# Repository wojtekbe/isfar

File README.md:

isfar - H-ROV underwater robot
=====

Connectors
==========

I^2C (MICROMATCH-4):
--------
* 1 - SDA
* 2 - SCL
* 3 - GND
* 4 - +3V3

PWR (TBMP/C-GRID-03):
--------
* 1 - +5V
* 2 - GND
* 3 - +12V

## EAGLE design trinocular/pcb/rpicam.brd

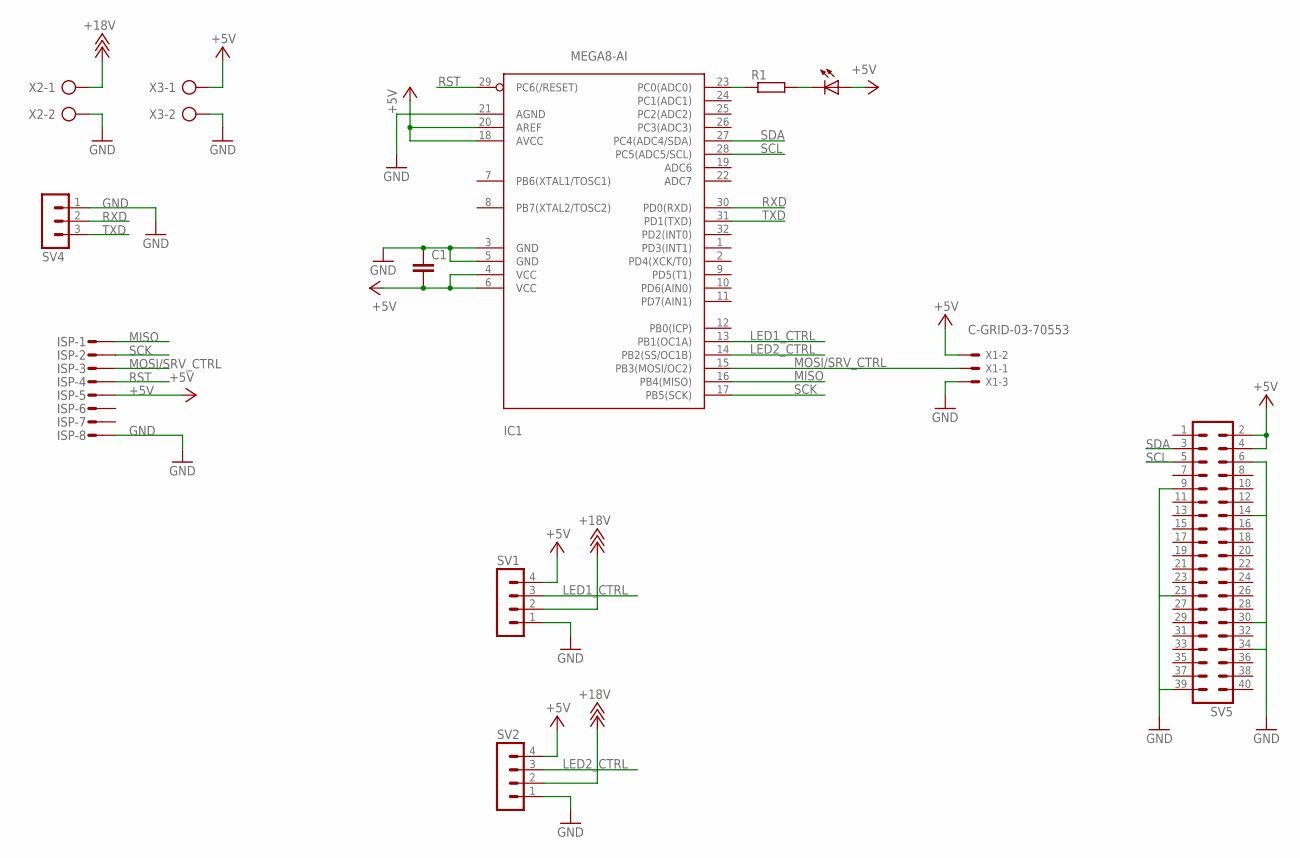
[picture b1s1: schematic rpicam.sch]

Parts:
C1: C-EUC0805; C0805
IC1: MEGA8-AI; TQFP32-08
ISP: MICROMATCH-8
LED1: LEDCHIP-LED0805; CHIP-LED0805
R1: R-EU_R0805; R0805
SV1, SV2: MA04-1
SV4: MA03-1
SV5: MA20-2
X1: C-GRID-03-70553; 70553-03
X2, X3: AK500/2

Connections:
+5V: C1.2, IC1.4 (VCC), IC1.6 (VCC), IC1.18 (AVCC), IC1.20 (AREF), ISP.5, LED1.A, SV1.4, SV2.4, SV5.2, SV5.4, X1.2, X3.1
+18V: SV1.2, SV2.2, X2.1
GND: C1.1, IC1.3 (GND), IC1.5 (GND), IC1.21 (AGND), ISP.8, SV1.1, SV2.1, SV4.1, SV5.6, SV5.9, SV5.14, SV5.25, SV5.30, SV5.34, SV5.39, X1.3, X2.2, X3.2
LED1_CTRL: IC1.13 (PB1(OC1A)), SV1.3
LED2_CTRL: IC1.14 (PB2(SS/OC1B)), SV2.3
MISO: IC1.16 (PB4(MISO)), ISP.1
MOSI/SRV_CTRL: IC1.15 (PB3(MOSI/OC2)), ISP.3, X1.1
unnamed: LED1.C, R1.2
unnamed: IC1.23 (PC0(ADC0)), R1.1
RST: IC1.29 (PC6(/RESET)), ISP.4
RXD: IC1.30 (PD0(RXD)), SV4.2
SCK: IC1.17 (PB5(SCK)), ISP.2
SCL: IC1.28 (PC5(ADC5/SCL)), SV5.5
SDA: IC1.27 (PC4(ADC4/SDA)), SV5.3
TXD: IC1.31 (PD1(TXD)), SV4.3

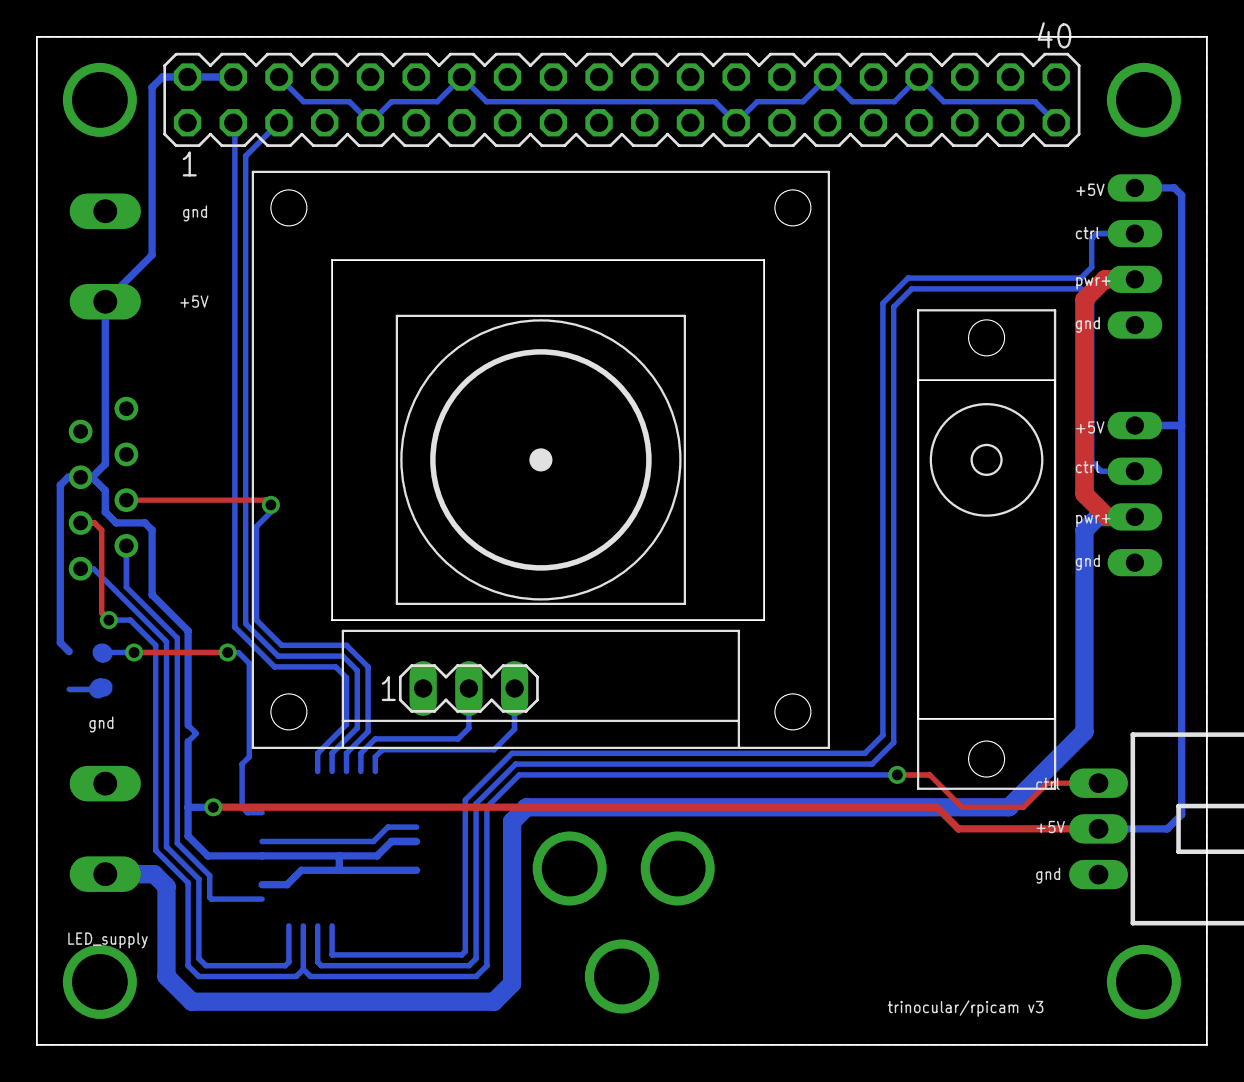
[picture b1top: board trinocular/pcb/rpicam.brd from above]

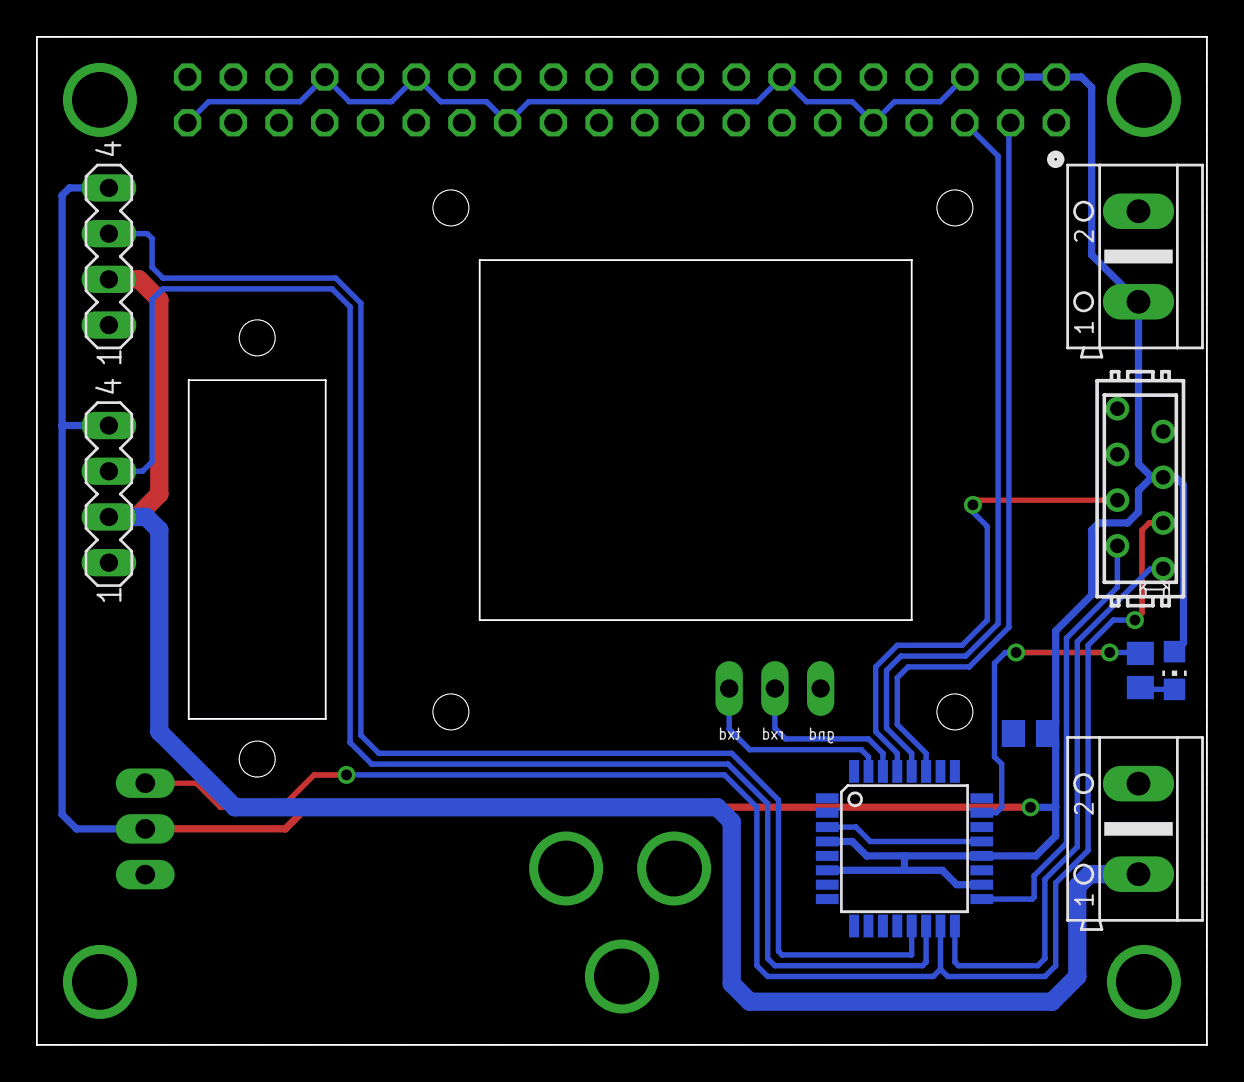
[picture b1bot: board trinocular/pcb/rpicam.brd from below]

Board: 2 copper layers, 65.0 x 56.0 mm, 14 parts (9 on the bottom side), 15 nets.

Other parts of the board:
U$3: HS-35HD
U$4: RPICAM_WAVESHARE

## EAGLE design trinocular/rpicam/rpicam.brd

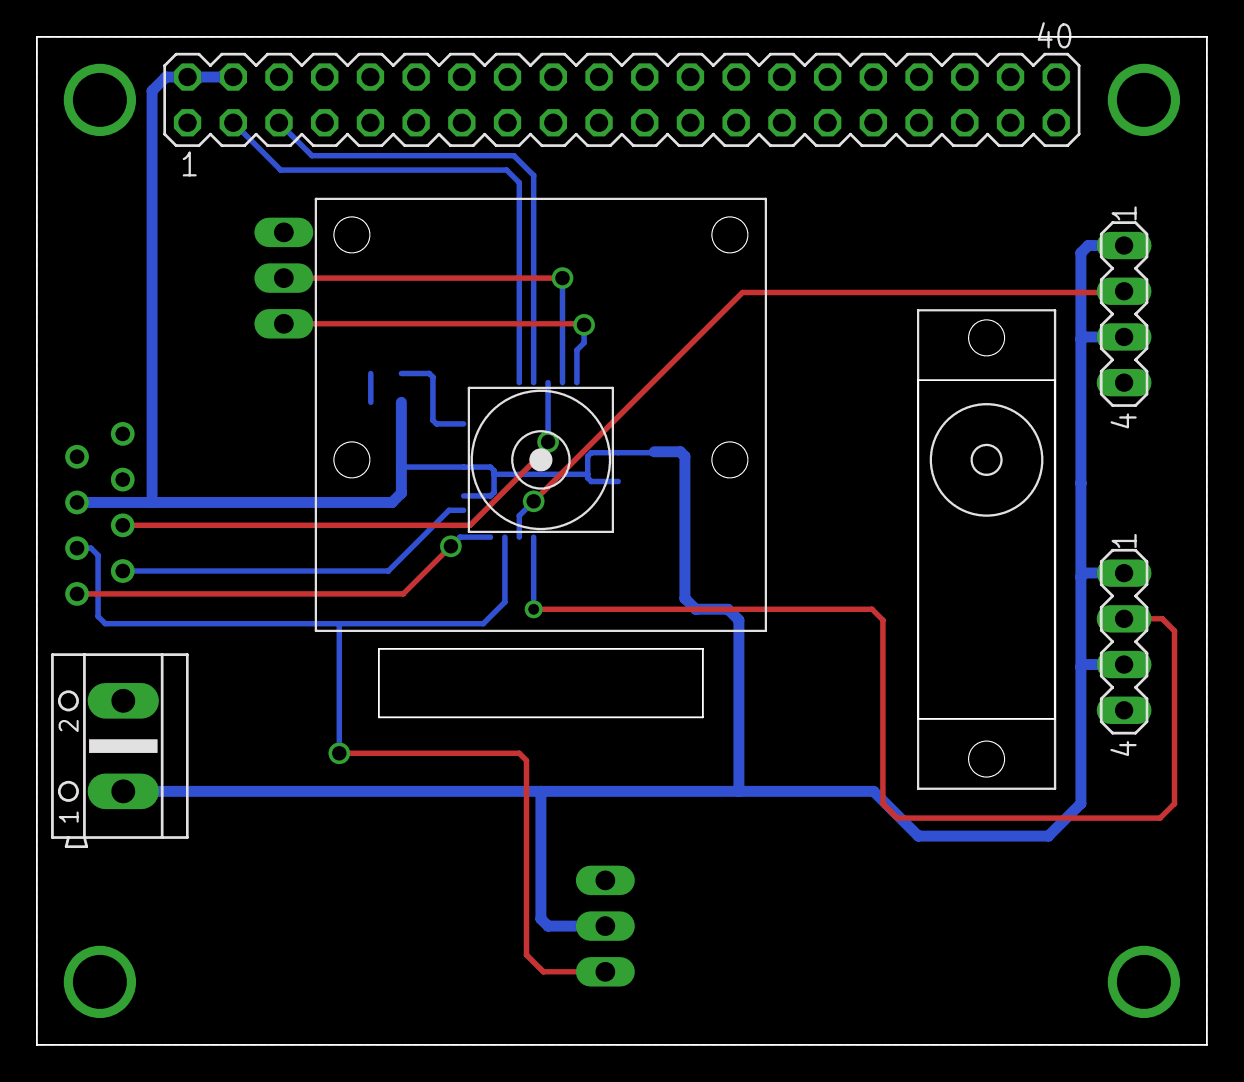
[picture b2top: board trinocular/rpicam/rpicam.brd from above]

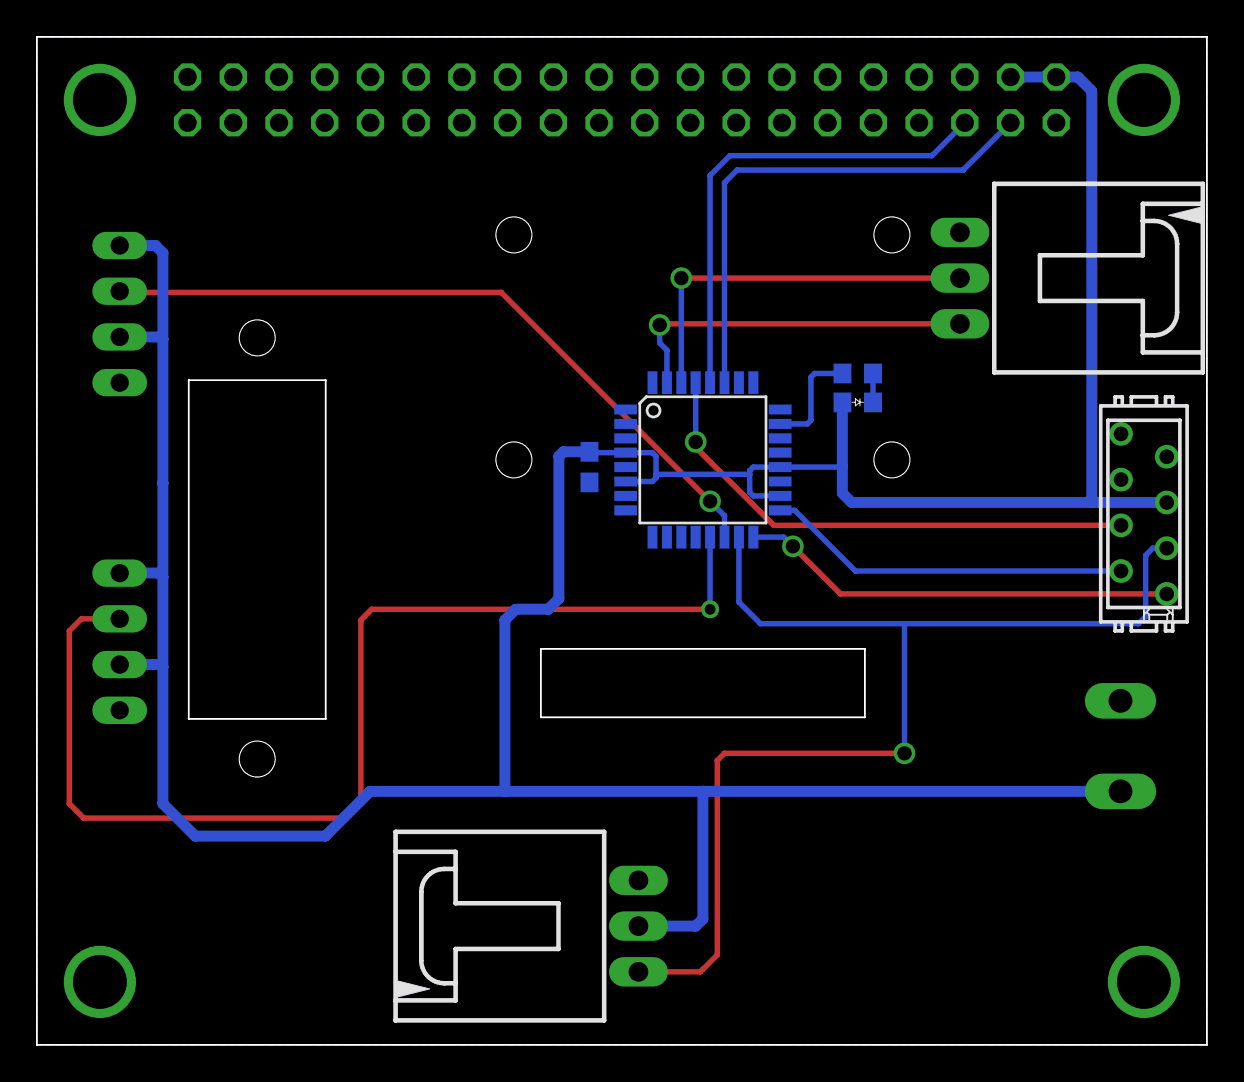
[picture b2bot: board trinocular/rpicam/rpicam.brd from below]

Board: 2 copper layers, 65.0 x 56.0 mm, 13 parts (7 on the bottom side), 14 nets.

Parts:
C1: C0603
IC1: MEGA8-AI; TQFP32-08
ISP: MICROMATCH-8
R1: R0603
SV1: MA20-2
SV2, SV3: MA04-1
U$1: LED0603; D0603
U$2: RPICAM
U$3: HS-35HD
UART: uart; 70553-03
X1: C-GRID-03-70553; 70553-03
X2: AK500/2

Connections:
+5V: C1.2, IC1.4, IC1.6, IC1.18, IC1.20, ISP.5, SV1.2, SV1.4, SV2.1, SV2.3, SV3.1, SV3.3, U$1.1, X1.2, X2.1
GND: C1.1, IC1.3, IC1.5, IC1.21, ISP.8, SV1.6, SV1.9, SV1.14, SV1.20, SV1.25, SV1.30, SV1.34, SV1.39, SV2.4, SV3.4, UART.1, X1.3, X2.2
LED1_CTRL: IC1.13, SV2.2
LED2_CTRL: IC1.14, SV3.2
MISO: IC1.16, ISP.1
MOSI/SRV_CTRL: IC1.15, ISP.3, X1.1
unnamed: R1.2, U$1.2
unnamed: IC1.23, R1.1
RST: IC1.29, ISP.4
RXD: IC1.30, UART.2
SCK: IC1.17, ISP.2
SCL: IC1.28, SV1.5
SDA: IC1.27, SV1.3
TXD: IC1.31, UART.3

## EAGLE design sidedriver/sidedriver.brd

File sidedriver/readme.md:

## GPIO Conf.

### M. Thruster

Name   | Pin | Func.
-------|-----|-----------
M1-PWM | PA1 | TIM2_CH2 
M1-CS  | PA2 | ADC123_IN2
M1-ENA | PC3 | out       
M1-ENB | PA3 | out        
M1-INA | PC3 | out        
M1-INB | PA4 | out        
ENC1   | PC6 | TIM8_CH1   
ENC2   | PC7 | TIM8_CH2   

### Piston Tank

Name   | Pin | Func.
-------|-----|----------
M2-PWM | PB0 | TIM1_CH2N
M2-ENA | PB1 | out
M2-ENB | PA6 | out 
M2-INA | PB2 | out
M2-INB | PA5 | out
TRANS  | PC8 | ?

### LED Driver

Name    | Pin  | Func.
--------|------|---------
SRV1    | PA8  | ?
SRV2    | PA11 | ?
LED-PWM | PC9  | TIM3_CH4

### USART Port

Name  | Pin  | Func.
------|------|----------
TX    | PA9  | USART1_TX
RX    | PA10 | USART1_RX

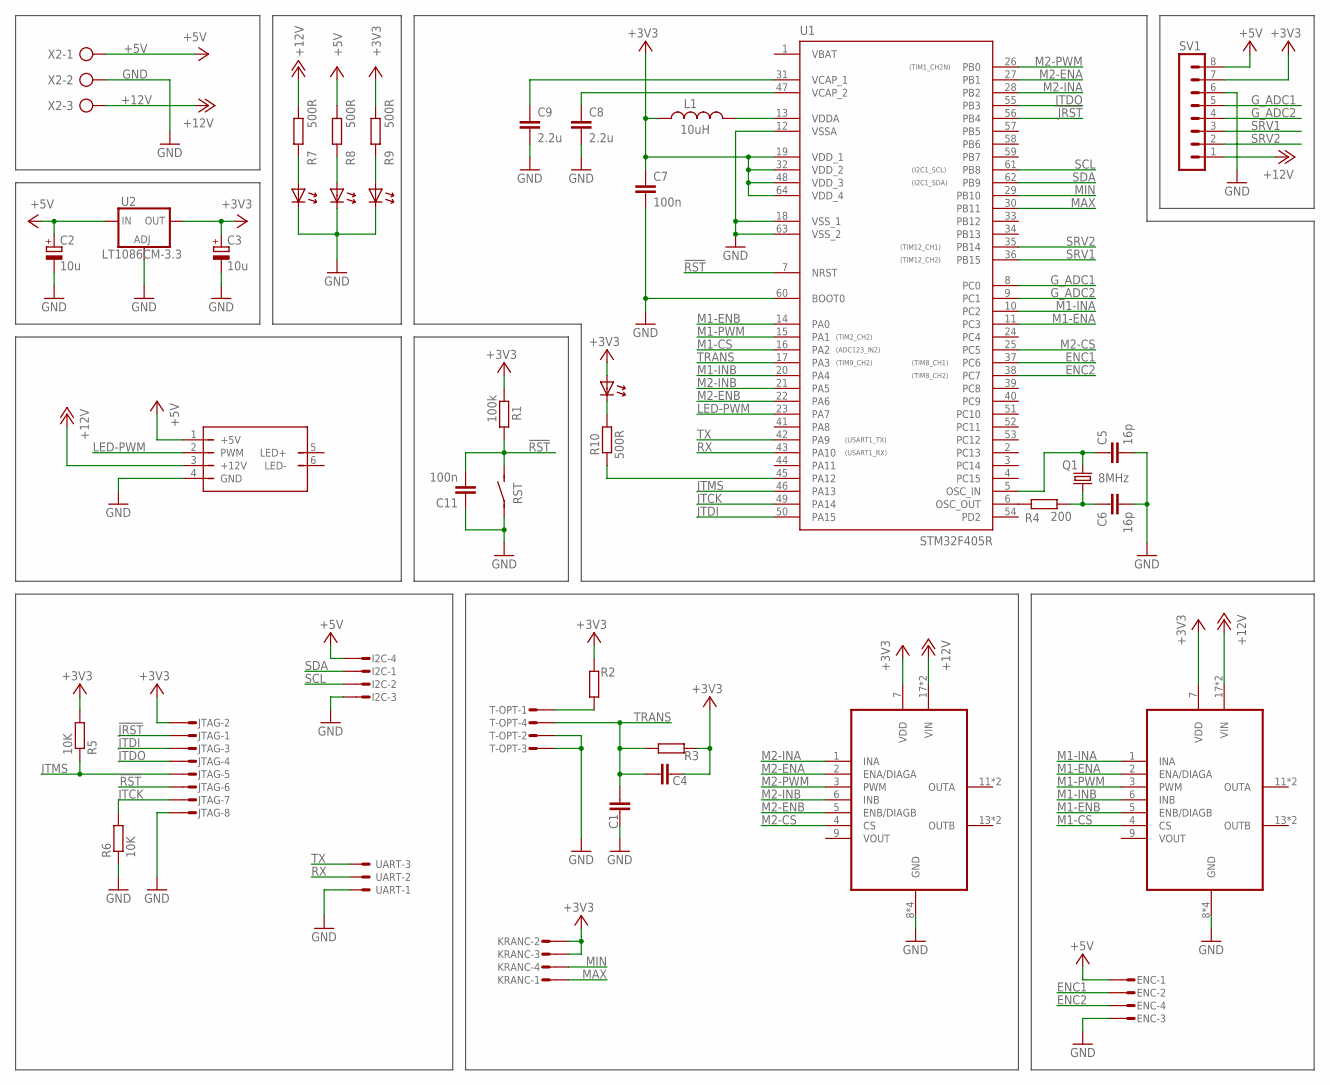
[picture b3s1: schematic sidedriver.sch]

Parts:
C1, C4: C-EUC0603; C0603
C2, C3: 10u; SMC_A
C5, C6: 16p; C0603
C7, C11: 100n; C0603
C8, C9: 2.2u; C0603
ENC: MICROMATCH-4
I2C: MICROMATCH-4
JTAG: MICROMATCH-8
KRANC: MICROMATCH-4
L1: 10uH; L0805
Q1: 8MHz; 12SMX
R1: 100k; R0603
R2, R3: R-EU_R0603; R0603
R4: 200; R0603
R5, R6: 10K; R0603
R7, R8, R9, R10: 500R; R0603
RST: TACT_SWITCH; SWITCH
SV1: MA08-1
T-OPT: MICROMATCH-4
U1: STM32F405R; TQFP64
U2: LT1086CM-3.3; D2PACK
U$2: LEDD1
U$3, U$4: POLOLU-1451
U$6, U$7, U$8, U$9: LED0603; D0603
UART: C-GRID-03-70543; 70543-03
X2: AK500/3

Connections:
!JRST: JTAG.1, U1.56 (PB4)
!RST: C11.2, JTAG.6, R1.2, RST.2 (S), RST.4 (S), U1.7 (NRST)
+3V3: C3.+, C4.1, C7.1, JTAG.2, KRANC.2, KRANC.3, L1.1, R1.1, R2.1, R3.1, R5.2, R9.1, SV1.7, U1.19 (VDD_1), U1.32 (VDD_2), U1.48 (VDD_3), U1.64 (VDD_4), U2.2 (OUT), U$3.7 (VDD), U$4.7 (VDD), U$9.1 (A)
+5V: C2.+, ENC.1, I2C.4, R8.1, SV1.8, U2.3 (IN), U$2.1 (+5V), X2.1
+12V: R7.1, SV1.1, U$2.3 (+12V), U$3.17 (VIN), U$3.18 (VIN), U$4.17 (VIN), U$4.18 (VIN), X2.3
ENC1: ENC.2, U1.37 (PC6)
ENC2: ENC.4, U1.38 (PC7)
GND: C1.1, C2.-, C3.-, C5.2, C6.2, C7.2, C8.2, C9.2, C11.1, ENC.3, I2C.3, JTAG.8, R6.1, RST.1, RST.3, SV1.6, T-OPT.2, T-OPT.3, U1.12 (VSSA), U1.18 (VSS_1), U1.60 (BOOT0), U1.63 (VSS_2), U2.1 (ADJ), U$2.4 (GND), U$3.8 (GND), U$3.10 (GND), U$3.15 (GND), U$3.16 (GND), U$4.8 (GND), U$4.10 (GND), U$4.15 (GND), U$4.16 (GND), U$6.2 (C), U$7.2 (C), U$8.2 (C), UART.1, X2.2
G_ADC1: SV1.5, U1.8 (PC0)
G_ADC2: SV1.4, U1.9 (PC1)
JTCK: JTAG.7, R6.2, U1.49 (PA14)
JTDI: JTAG.3, U1.50 (PA15)
JTDO: JTAG.4, U1.55 (PB3)
JTMS: JTAG.5, R5.1, U1.46 (PA13)
LED-PWM: U1.23 (PA7), U$2.2 (PWM)
M1-CS: U1.16 (PA2), U$4.4 (CS)
M1-ENA: U1.11 (PC3), U$4.2 (ENA/DIAGA)
M1-ENB: U1.14 (PA0), U$4.5 (ENB/DIAGB)
M1-INA: U1.10 (PC2), U$4.1 (INA)
M1-INB: U1.20 (PA4), U$4.6 (INB)
M1-PWM: U1.15 (PA1), U$4.3 (PWM)
M2-CS: U1.25 (PC5), U$3.4 (CS)
M2-ENA: U1.27 (PB1), U$3.2 (ENA/DIAGA)
M2-ENB: U1.22 (PA6), U$3.5 (ENB/DIAGB)
M2-INA: U1.28 (PB2), U$3.1 (INA)
M2-INB: U1.21 (PA5), U$3.6 (INB)
M2-PWM: U1.26 (PB0), U$3.3 (PWM)
MAX: KRANC.1, U1.30 (PB11)
MIN: KRANC.4, U1.29 (PB10)
unnamed: R2.2, T-OPT.1
unnamed: C6.1, Q1.1, R4.2
unnamed: C5.1, Q1.3 (2), U1.5 (OSC_IN)
unnamed: R7.2, U$6.1 (A)
unnamed: R8.2, U$7.1 (A)
unnamed: R9.2, U$8.1 (A)
unnamed: R10.2, U$9.2 (C)
unnamed: R10.1, U1.45 (PA12)
unnamed: L1.2, U1.13 (VDDA)
unnamed: R4.1, U1.6 (OSC_OUT)
unnamed: C8.1, U1.47 (VCAP_2)
unnamed: C9.1, U1.31 (VCAP_1)
RX: U1.43 (PA10), UART.2
SCL: I2C.2, U1.61 (PB8)
SDA: I2C.1, U1.62 (PB9)
SRV1: SV1.3, U1.36 (PB15)
SRV2: SV1.2, U1.35 (PB14)
TRANS: C1.2, C4.2, R3.2, T-OPT.4, U1.17 (PA3)
TX: U1.42 (PA9), UART.3

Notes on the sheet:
(ADC123_IN2)
(TIM1_CH2N)
(TIM2_CH2)
(TIM8_CH1)
(TIM8_CH2)
(I2C1_SDA)
(I2C1_SCL)
(USART1_TX)
(USART1_RX)
(TIM12_CH1)
(TIM12_CH2)
(TIM9_CH2)

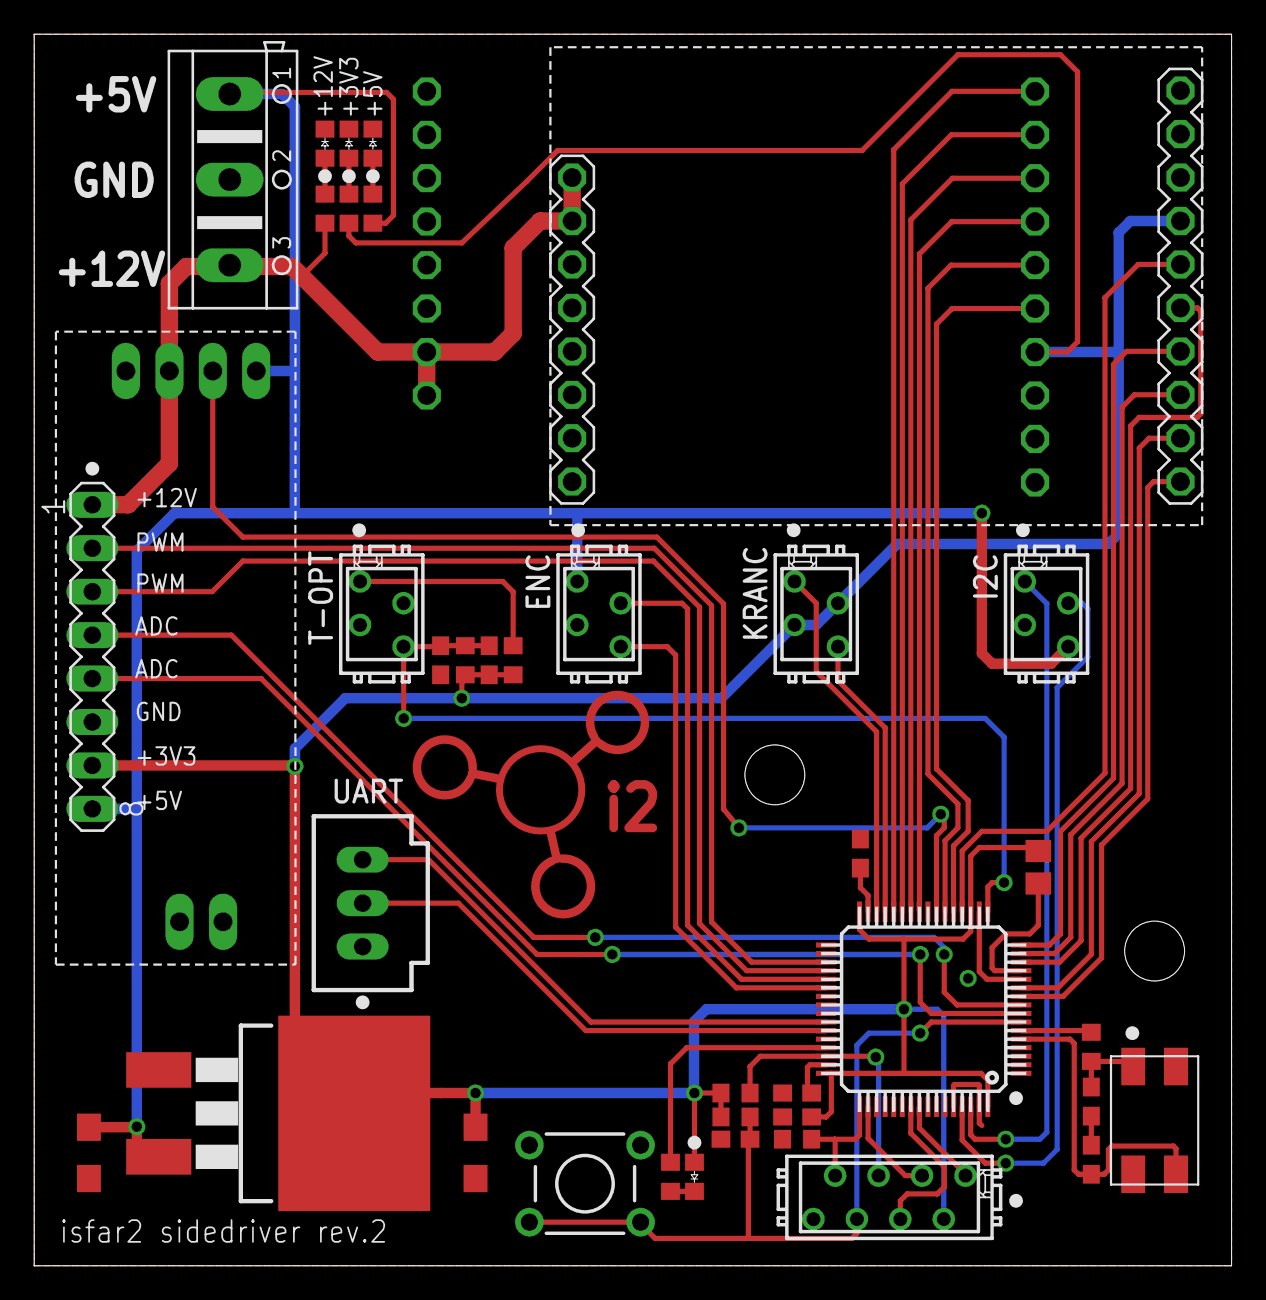
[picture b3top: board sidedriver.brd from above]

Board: 2 copper layers, 70.0 x 72.0 mm, 41 parts (1 on the bottom side), 48 nets.

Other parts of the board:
U$5: I2-LOGO

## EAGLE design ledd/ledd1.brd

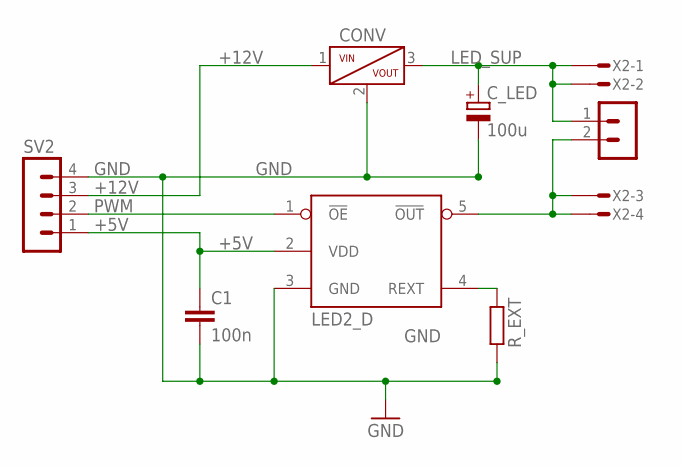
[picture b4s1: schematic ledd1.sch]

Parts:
C1: 100n; C0603
CONV: POLOLU-799
C_LED: 100u; E2-4
LED2_D: LED1_drv; TO-265
R_EXT: R-EU_R0603; R0603
SV2: MA04-1
SV3: MA02-1; MA03-1
X2: LEDOUT; MICROMATCH-4

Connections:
+5V: C1.1, LED2_D.2 (VDD), SV2.1
+12V: CONV.1 (VIN), SV2.3
GND: C1.2, CONV.2 (GND), C_LED.-, LED2_D.3 (GND), LED2_D.6 (GND), R_EXT.2, SV2.4
LED_SUP: CONV.3 (VOUT), C_LED.+, SV3.1, X2.1, X2.2
unnamed: LED2_D.4 (REXT), R_EXT.1
unnamed: LED2_D.5 (!OUT), SV3.2, X2.3, X2.4
PWM: LED2_D.1 (!OE), SV2.2

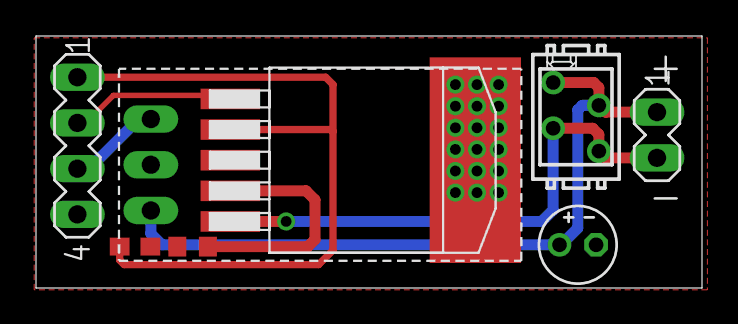
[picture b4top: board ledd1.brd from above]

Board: 2 copper layers, 37.0 x 14.0 mm, 8 parts (0 on the bottom side), 7 nets.

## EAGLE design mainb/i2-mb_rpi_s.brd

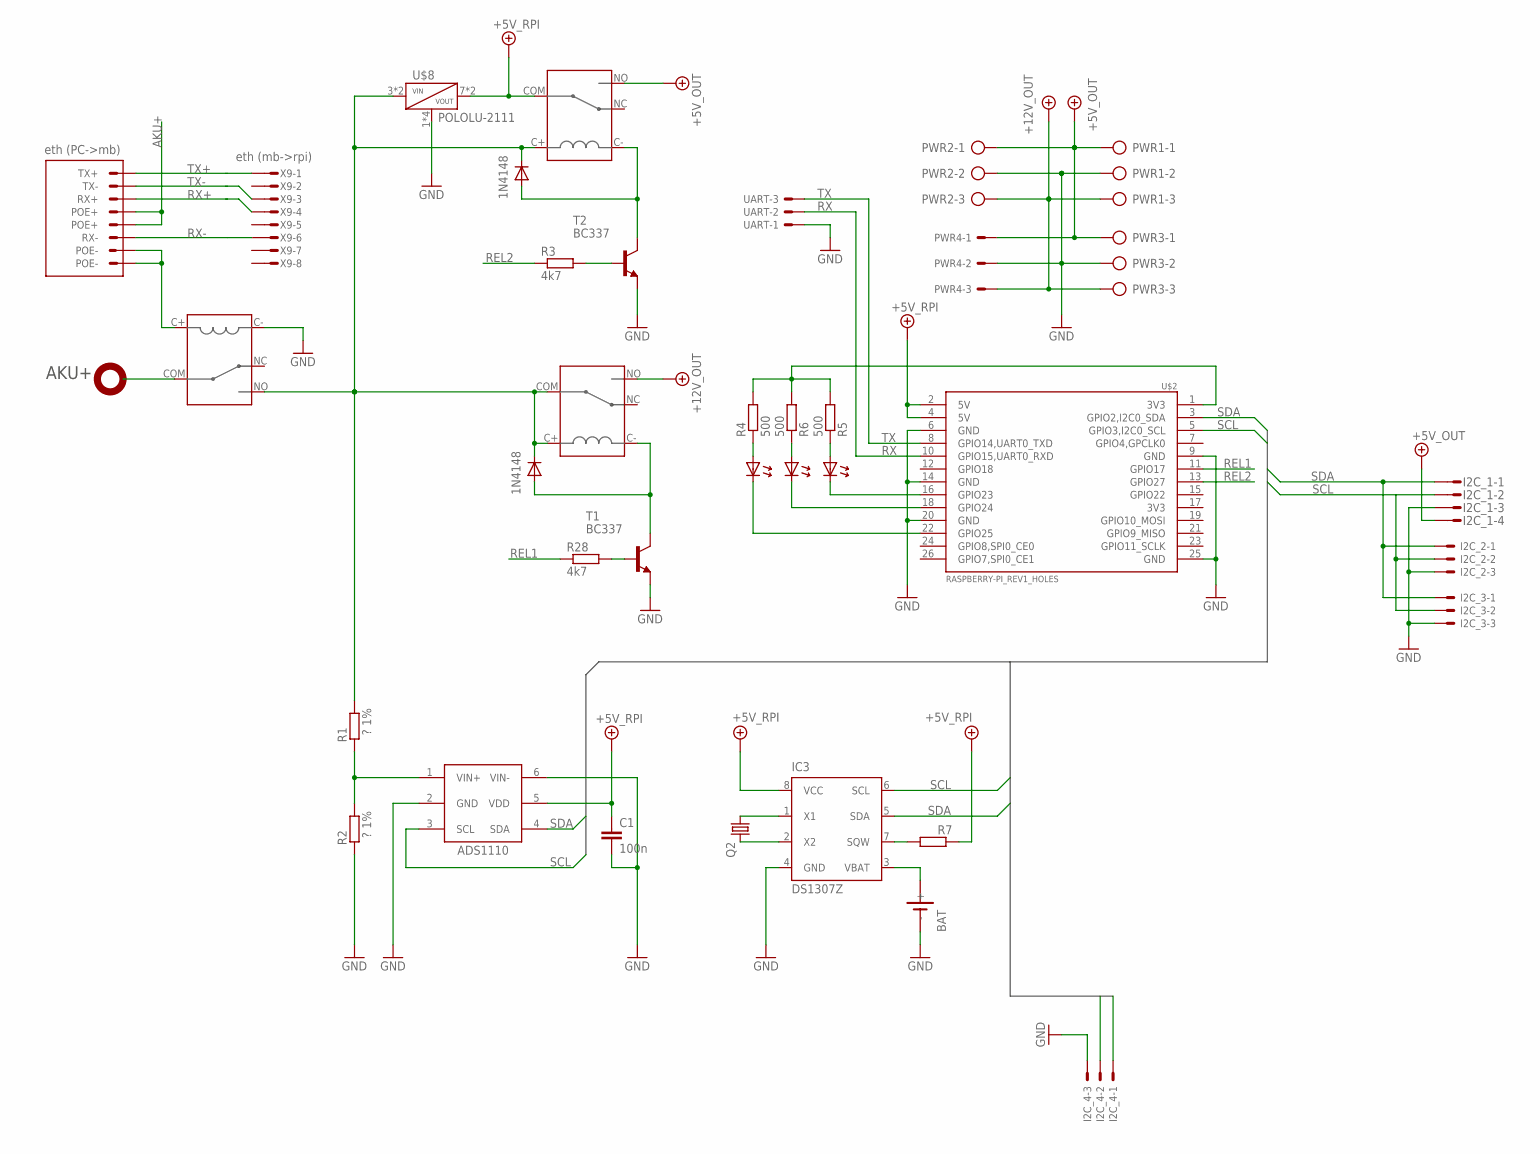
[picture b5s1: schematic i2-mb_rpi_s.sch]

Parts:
BAT: SN2032
C1: 100n; C0603
I2C_1: MICROMATCH-4
I2C_2, I2C_3, I2C_4: C-GRID-03-70553; 70553-03
IC1: ADS1110; SOT-23-6
IC3: DS1307Z; SOIC8
LED1, LED2, LED3: LED0603; D0603
PWR1, PWR2, PWR3: TBMP5103RC-KFV1; TBMP5103RC-KF
PWR4: C-GRID-03-70543; 70543-03
Q2: CRYSTAL; CFPX-217
R1, R2: ? 1%; R0603
R3, R28: 4k7; R0603
R4, R5, R6: 500; R0603
R7: R-EU_R0603; R0603
T1, T2: BC337; TO92
U$2: RASPBERRY-PI_REV1_HOLES; RASPBERRY-PI_HOLES
U$3, U$4: 1N4148; D0603
U$5, U$6, U$7: FBR51; PC_RELAY
U$8: POLOLU-2111
UART: C-GRID-03-70543; 70543-03
X9: eth (mb->rpi); MICROMATCH-8
X_ETH: eth (PC->mb); 8P8C-TOP

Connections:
+5V: I2C_1.4, PWR1.1, PWR2.1, PWR3.1, PWR4.1, U$5.NO
+5V_RPI: C1.1, IC1.5 (VDD), IC3.8 (VCC), R7.1, U$2.2 (5V), U$2.4 (5V), U$5.COM, U$8.7 (VOUT), U$8.8 (VOUT)
+12V_IN: R1.1, U$3.2 (C), U$4.2 (C), U$5.C+, U$6.NO, U$7.C+, U$7.COM, U$8.3 (VIN), U$8.4 (VIN)
+12V_OUT: PWR1.3, PWR2.3, PWR3.3, PWR4.3, U$7.NO
AKU+: U$6.COM, X_ETH.4 (POE+), X_ETH.5 (POE+)
GND: BAT.-, C1.2, I2C_1.3, I2C_2.3, I2C_3.3, I2C_4.3, IC1.2 (GND), IC1.6 (VIN-), IC3.4 (GND), PWR1.2, PWR2.2, PWR3.2, PWR4.2, R2.2, T1.1 (E), T2.1 (E), U$2.6 (GND), U$2.9 (GND), U$2.14 (GND), U$2.20 (GND), U$2.25 (GND), U$6.C-, U$8.1 (GND), U$8.2 (GND), U$8.5 (GND), U$8.6 (GND), UART.1
LED2: LED2.2 (C), U$2.16 (GPIO23)
LED3: LED3.2 (C), U$2.18 (GPIO24)
unnamed: R3.2, T2.2 (B)
unnamed: T2.3 (C), U$3.1 (A), U$5.C-
unnamed: BAT.+, IC3.3 (VBAT)
unnamed: LED2.1 (A), R5.1
unnamed: LED1.1 (A), R4.1
unnamed: IC3.1 (X1), Q2.1
unnamed: LED1.2 (C), U$2.22 (GPIO25)
unnamed: LED3.1 (A), R6.1
unnamed: IC3.2 (X2), Q2.2
unnamed: IC3.7 (SQW), R7.2
unnamed: R4.2, R5.2, R6.2, U$2.1 (3V3)
unnamed: T1.3 (C), U$4.1 (A), U$7.C-
unnamed: R28.2, T1.2 (B)
POE-: U$6.C+, X_ETH.7 (POE-), X_ETH.8 (POE-)
REL1: R28.1, U$2.11 (GPIO17)
REL2: R3.1, U$2.13 (GPIO27)
RX: U$2.10 (GPIO15,UART0_RXD), UART.2
RX+: X9.4, X_ETH.3 (RX+)
RX-: X9.6, X_ETH.6 (RX-)
SCL: I2C_1.2, I2C_2.2, I2C_3.2, I2C_4.2, IC1.3 (SCL), IC3.6 (SCL), U$2.5 (GPIO3,I2C0_SCL)
SDA: I2C_1.1, I2C_2.1, I2C_3.1, I2C_4.1, IC1.4 (SDA), IC3.5 (SDA), U$2.3 (GPIO2,I2C0_SDA)
TX: U$2.8 (GPIO14,UART0_TXD), UART.3
TX+: X9.1, X_ETH.1 (TX+)
TX-: X9.3, X_ETH.2 (TX-)
V_SENS: IC1.1 (VIN+), R1.2, R2.1

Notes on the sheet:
AKU+

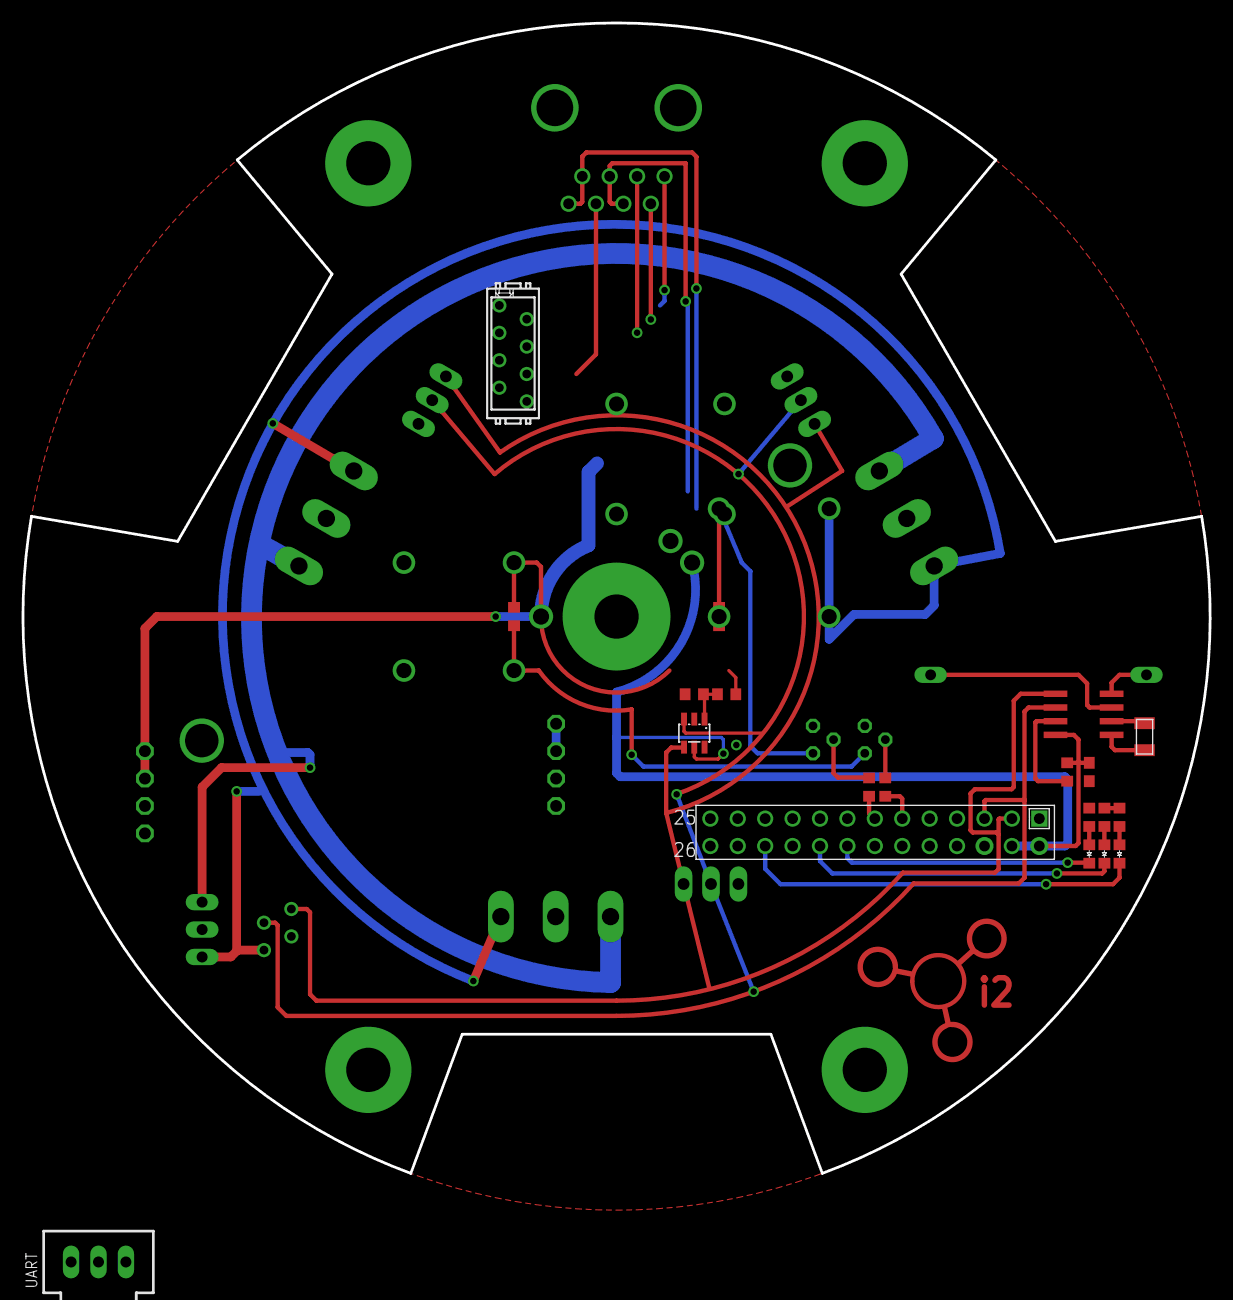
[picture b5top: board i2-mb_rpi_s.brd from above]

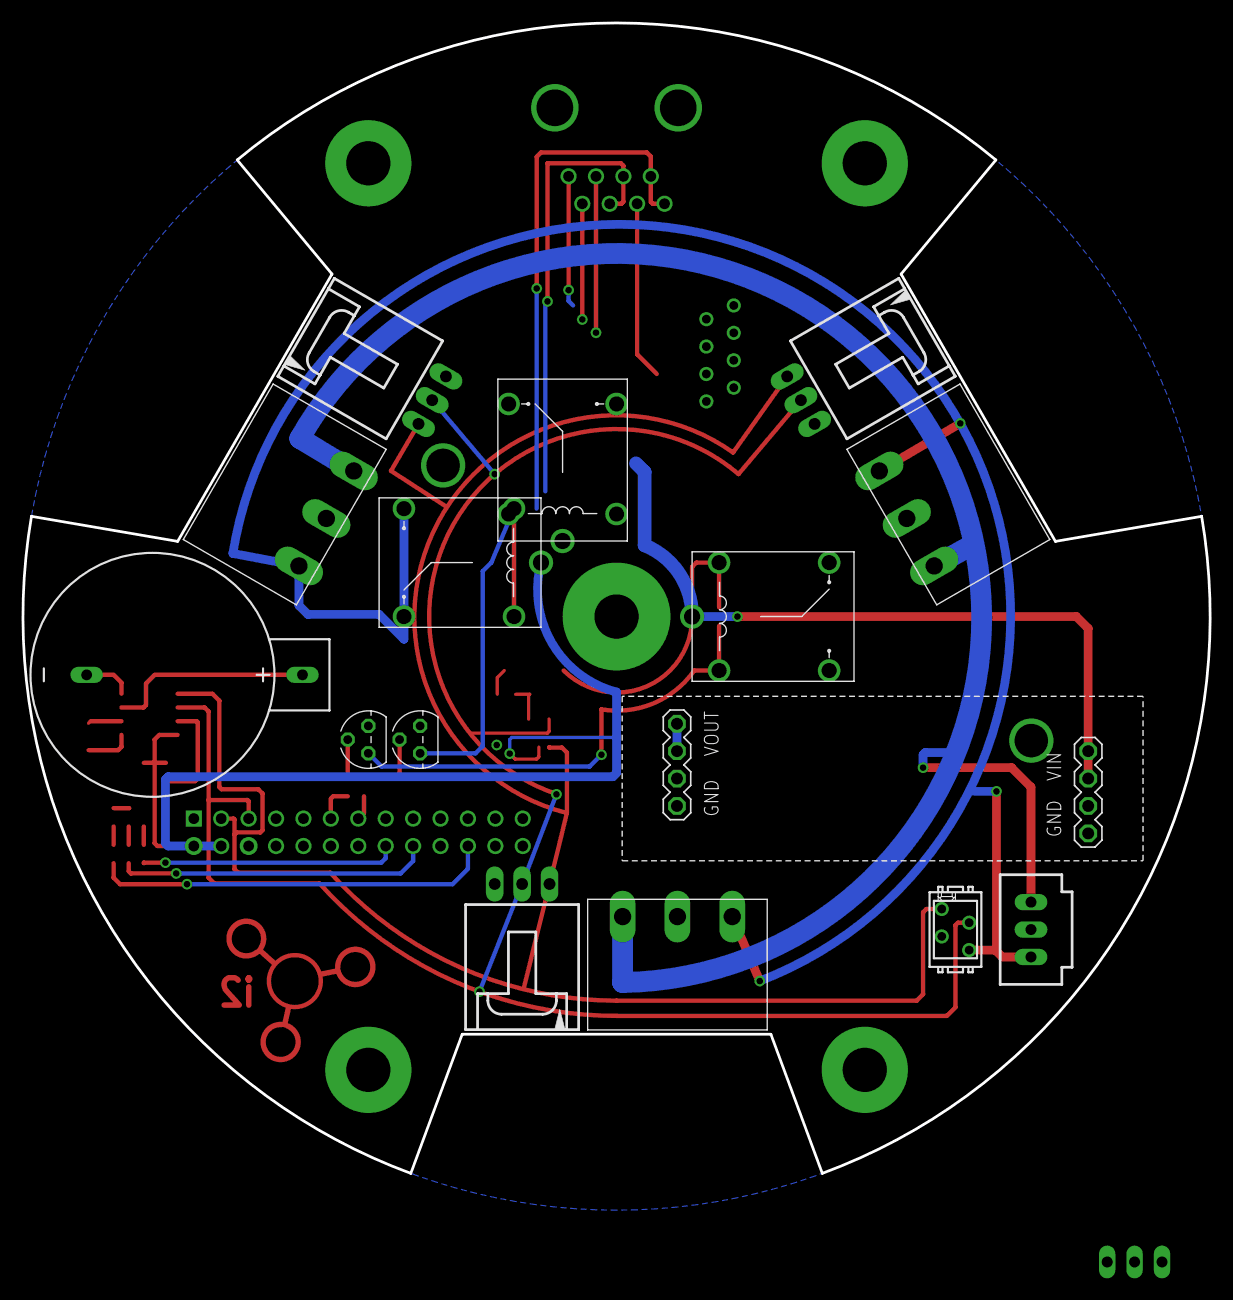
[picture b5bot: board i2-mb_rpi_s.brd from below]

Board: 2 copper layers, 110.0 x 106.6 mm, 37 parts (15 on the bottom side), 33 nets.

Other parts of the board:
U$1: I2-LOGO
